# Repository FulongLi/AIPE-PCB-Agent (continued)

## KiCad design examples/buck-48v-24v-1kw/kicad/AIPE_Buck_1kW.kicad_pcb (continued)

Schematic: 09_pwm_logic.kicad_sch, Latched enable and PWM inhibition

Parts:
C69, C70, C71, C72: 100n/50V; C_0805_2012Metric
R51, R52: 33; R_0805_2012Metric
R53, R54, R55: 10k; R_0805_2012Metric
U12: SN74LVC1G74DCTR; SSOP-8_2.95x2.8mm_P0.65mm
U13: SN74LVC1G86DBVR; SOT-23-5
U14: SN74LVC1G08DBVR; SOT-23-5
U15: SN74LVC2G08DCTR; SSOP-8_2.95x2.8mm_P0.65mm

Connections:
3V3: C69.1, C70.1, C71.1, C72.1, U12.2 (D), U12.7 (PRE_N), U12.8 (VCC), U13.5 (VCC), U14.5 (VCC), U15.8 (VCC); also elsewhere on the board
ARM: R55.1, U12.1 (CLK); also elsewhere on the board
ARMED: U12.5 (Q), U14.1 (A); also elsewhere on the board
FAULT_N: U12.6 (CLR_N); also elsewhere on the board
GATE_OK: U14.4 (Y), U15.2 (1B), U15.6 (2B)
GND: C69.2, C70.2, C71.2, C72.2, R53.2, R54.2, R55.2, U12.4 (GND), U13.3 (GND), U14.3 (GND), U15.4 (GND); also elsewhere on the board
HI: R51.2; also elsewhere on the board
HI_LOGIC: R51.1, U15.7 (1Y)
LI: R52.2; also elsewhere on the board
LI_LOGIC: R52.1, U15.3 (2Y)
PWM_EXCLUSIVE: U13.4 (Y), U14.2 (B)
PWM_H: R53.1, U13.1 (A), U15.1 (1A); also elsewhere on the board
PWM_L: R54.1, U13.2 (B), U15.5 (2A); also elsewhere on the board

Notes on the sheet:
Latched enable and PWM inhibition

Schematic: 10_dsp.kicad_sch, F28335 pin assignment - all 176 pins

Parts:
U16: TMS320F28335PGFA; LQFP-176_24x24mm_P0.5mm

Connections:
1V9: U16.4 (VDD), U16.15 (VDD), U16.23 (VDD), U16.29 (VDD), U16.31 (VDD1A18), U16.59 (VDD2A18), U16.61 (VDD), U16.101 (VDD), U16.109 (VDD), U16.117 (VDD), U16.126 (VDD), U16.139 (VDD), U16.146 (VDD), U16.154 (VDD), U16.167 (VDD); also elsewhere on the board
3V3: U16.9 (VDDIO), U16.34 (VDDA2), U16.45 (VDDAIO), U16.71 (VDDIO), U16.84 (VDD3VFL), U16.93 (VDDIO), U16.107 (VDDIO), U16.121 (VDDIO), U16.143 (VDDIO), U16.159 (VDDIO), U16.170 (VDDIO); also elsewhere on the board
ADCBIAS: U16.57 (ADCRESEXT); also elsewhere on the board
ADCREFM: U16.55 (ADCREFM); also elsewhere on the board
ADCREFP: U16.56 (ADCREFP); also elsewhere on the board
ADC_CURRENT: U16.40 (ADCINA2); also elsewhere on the board
ADC_TEMP: U16.39 (ADCINA3); also elsewhere on the board
ADC_VIN: U16.42 (ADCINA0); also elsewhere on the board
ADC_VOUT: U16.41 (ADCINA1); also elsewhere on the board
ARM: U16.7 (GPIO2); also elsewhere on the board
BOOT84: U16.169 (GPIO84); also elsewhere on the board
BOOT85: U16.172 (GPIO85); also elsewhere on the board
BOOT86: U16.173 (GPIO86); also elsewhere on the board
BOOT87: U16.174 (GPIO87); also elsewhere on the board
CLK30: U16.105 (XCLKIN); also elsewhere on the board
EMU0: U16.85 (EMU0); also elsewhere on the board
EMU1: U16.86 (EMU1); also elsewhere on the board
FAULT_N: U16.21 (GPIO12); also elsewhere on the board
GND: U16.3 (VSS), U16.8 (VSS), U16.14 (VSS), U16.22 (VSS), U16.30 (VSS), U16.32 (VSS1AGND), U16.33 (VSSA2), U16.35 (ADCINA7), U16.36 (ADCINA6), U16.37 (ADCINA5), U16.38 (ADCINA4), U16.43 (ADCLO), U16.44 (VSSAIO), U16.46 (ADCINB0), U16.47 (ADCINB1), U16.48 (ADCINB2), U16.49 (ADCINB3), U16.50 (ADCINB4), U16.51 (ADCINB5), U16.52 (ADCINB6), U16.53 (ADCINB7), U16.54 (ADCREFIN), U16.58 (VSS2AGND), U16.60 (VSS), U16.70 (VSS), U16.83 (VSS), U16.92 (VSS), U16.103 (VSS), U16.104 (X1), U16.106 (VSS), U16.108 (VSS), U16.118 (VSS), U16.120 (VSS), U16.125 (VSS), U16.140 (VSS), U16.144 (VSS), U16.147 (VSS), U16.155 (VSS), U16.160 (VSS), U16.166 (VSS), U16.171 (VSS); also elsewhere on the board
PWM_H: U16.5 (GPIO0); also elsewhere on the board
PWM_L: U16.6 (GPIO1); also elsewhere on the board
TCK: U16.87 (TCK); also elsewhere on the board
TDI: U16.76 (TDI); also elsewhere on the board
TDO: U16.77 (TDO); also elsewhere on the board
TMS: U16.79 (TMS); also elsewhere on the board
TRST: U16.78 (TRST); also elsewhere on the board
UART_RX: U16.141 (GPIO28); also elsewhere on the board
UART_TX: U16.2 (GPIO29); also elsewhere on the board
XRS_N: U16.80 (XRS); also elsewhere on the board

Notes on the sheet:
F28335 pin assignment - all 176 pins
Units: supply pins / ADC / connected digital pins / intentionally unused digital pins. TEST1, TEST2 and X2 are NC.

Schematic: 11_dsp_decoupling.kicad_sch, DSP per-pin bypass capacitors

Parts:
C73, C74, C75, C76, C77, C78, C79, C80, C81, C82, C83, C84, C85, C86, C87, C88, C89, C90, C91, C92, C93, C94, C95, C96, C97, C98: 100n/50V; C_0805_2012Metric
C99, C100, C101, C102: 2.2u/25V; C_0805_2012Metric

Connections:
1V9: C73.1, C75.1, C76.1, C77.1, C78.1, C81.1, C82.1, C86.1, C88.1, C89.1, C91.1, C92.1, C94.1, C95.1, C97.1, C99.1, C100.1; also elsewhere on the board
3V3: C74.1, C79.1, C80.1, C83.1, C84.1, C85.1, C87.1, C90.1, C93.1, C96.1, C98.1, C101.1, C102.1; also elsewhere on the board
GND: C73.2, C74.2, C75.2, C76.2, C77.2, C78.2, C79.2, C80.2, C81.2, C82.2, C83.2, C84.2, C85.2, C86.2, C87.2, C88.2, C89.2, C90.2, C91.2, C92.2, C93.2, C94.2, C95.2, C96.2, C97.2, C98.2, C99.2, C100.2, C101.2, C102.2; also elsewhere on the board

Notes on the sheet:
DSP per-pin bypass capacitors

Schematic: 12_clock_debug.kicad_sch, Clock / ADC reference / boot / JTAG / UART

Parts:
C103, C104: 2.2u/25V; C_0805_2012Metric
C105: 100n/50V; C_0805_2012Metric
J7: TI 14-pin JTAG; key pin 6 absent; PinHeader_2x07_P2.54mm_Vertical
J8: BOOT: 1-2 SCI / 2-3 or open Flash; PinHeader_1x03_P2.54mm_Vertical
J9: UART 3.3 V only; PinHeader_1x03_P2.54mm_Vertical
R56: 22k; R_0805_2012Metric
R57: 33; R_0805_2012Metric
R58, R59, R60, R61, R62, R63, R64, R65: 4.7k; R_0805_2012Metric
R66: 2.2k; R_0805_2012Metric
R67, R68: 10k; R_0805_2012Metric
Y1: 30MHz/3V3; Oscillator_SMD_SeikoEpson_SG8002CA-4Pin_7.0x5.0mm

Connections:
3V3: C105.1, J7.5, J8.3, R58.1, R59.1, R60.1, R61.1, R62.1, R63.1, R64.1, R65.1, R68.1, Y1.1 (OE), Y1.4 (VDD); also elsewhere on the board
ADCBIAS: R56.1; also elsewhere on the board
ADCREFM: C103.1; also elsewhere on the board
ADCREFP: C104.1; also elsewhere on the board
BOOT84: J8.2, R58.2; also elsewhere on the board
BOOT85: R59.2; also elsewhere on the board
BOOT86: R60.2; also elsewhere on the board
BOOT87: R61.2; also elsewhere on the board
CLK30: R57.2; also elsewhere on the board
CLK30_SOURCE: R57.1, Y1.3 (OUT)
EMU0: J7.13, R62.2; also elsewhere on the board
EMU1: J7.14, R63.2; also elsewhere on the board
GND: C103.2, C104.2, C105.2, J7.4, J7.8, J7.10, J7.12, J8.1, J9.3, R56.2, R66.2, R67.2, Y1.2 (GND); also elsewhere on the board
TCK: J7.9, J7.11, R67.1; also elsewhere on the board
TDI: J7.3, R65.2; also elsewhere on the board
TDO: J7.7; also elsewhere on the board
TMS: J7.1, R64.2; also elsewhere on the board
TRST: J7.2, R66.1; also elsewhere on the board
UART_RX: J9.2, R68.2; also elsewhere on the board
UART_TX: J9.1; also elsewhere on the board

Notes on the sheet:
Clock / ADC reference / boot / JTAG / UART

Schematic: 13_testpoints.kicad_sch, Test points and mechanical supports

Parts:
H1, H2, H3, H4, H5, H6, H7, H8: M3 support; MountingHole_3.2mm_M3
TP1: VIN; TestPoint_Pad_D2.0mm
TP2: VOUT; TestPoint_Pad_D2.0mm
TP3: GND; TestPoint_Pad_D2.0mm
TP4: AUX12; TestPoint_Pad_D2.0mm
TP5: 5V; TestPoint_Pad_D2.0mm
TP6: 3V3; TestPoint_Pad_D2.0mm
TP7: 1V9; TestPoint_Pad_D2.0mm
TP8: FAULT_N; TestPoint_Pad_D2.0mm
TP9: ARMED; TestPoint_Pad_D2.0mm
TP10: ADC_CURRENT; TestPoint_Pad_D2.0mm
TP11: ADC_VOUT; TestPoint_Pad_D2.0mm
TP12: ADC_VIN; TestPoint_Pad_D2.0mm

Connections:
1V9: TP7.1; also elsewhere on the board
3V3: TP6.1; also elsewhere on the board
5V: TP5.1; also elsewhere on the board
ADC_CURRENT: TP10.1; also elsewhere on the board
ADC_VIN: TP12.1; also elsewhere on the board
ADC_VOUT: TP11.1; also elsewhere on the board
ARMED: TP9.1; also elsewhere on the board
AUX12: TP4.1; also elsewhere on the board
FAULT_N: TP8.1; also elsewhere on the board
GND: TP3.1; also elsewhere on the board
VIN: TP1.1; also elsewhere on the board
VOUT: TP2.1; also elsewhere on the board

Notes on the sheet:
Test points and mechanical supports
Flags: input source, fuse output, inductor output, auxiliary outputs through inductors, and bootstrap diode supply. They state supply provenance for ERC; they do not prove voltage, current capacity, or protection.

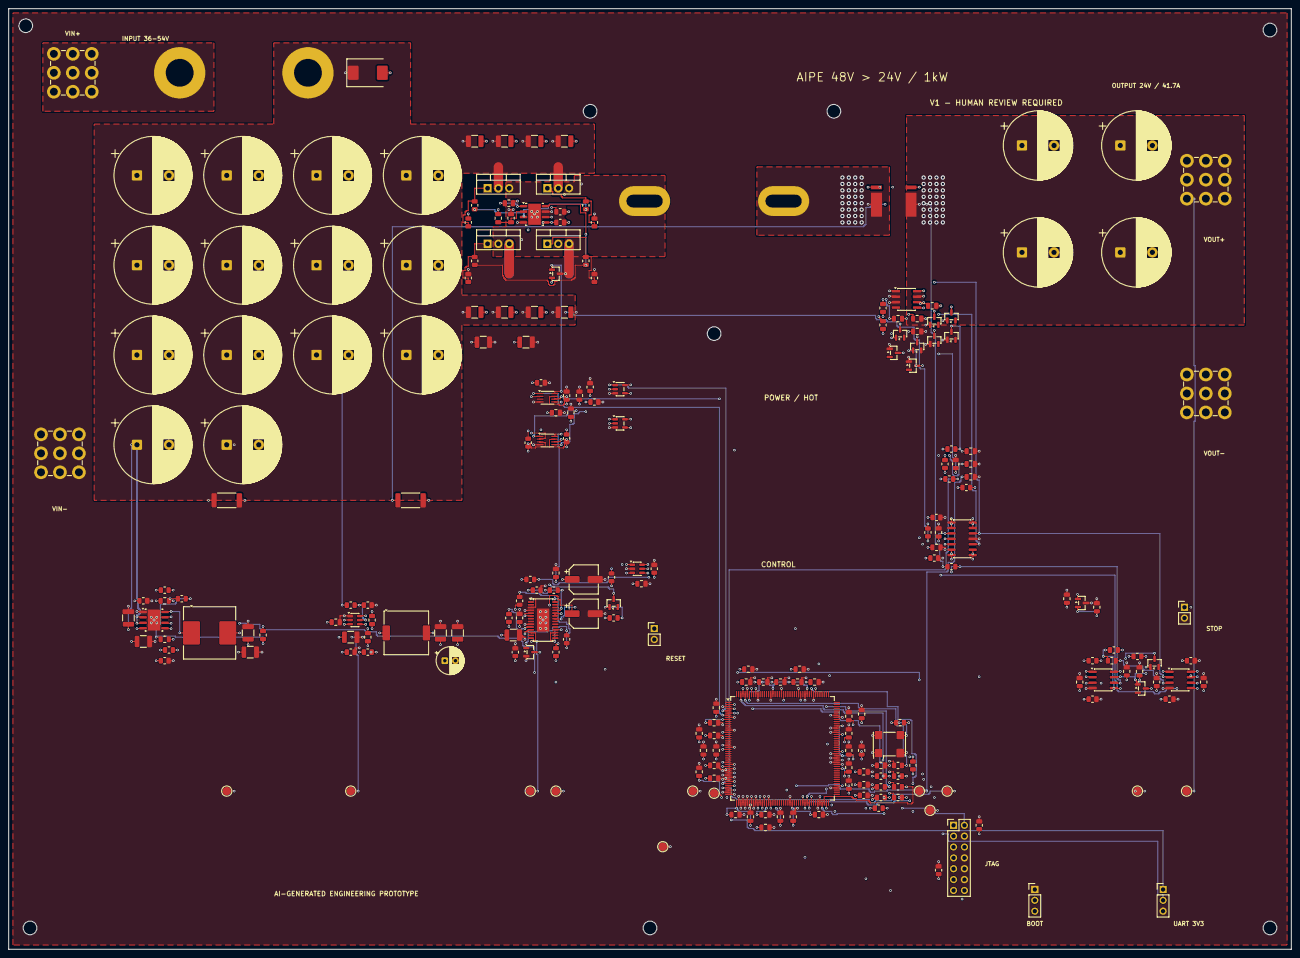
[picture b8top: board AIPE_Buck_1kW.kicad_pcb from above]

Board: 6 copper layers, 300.0 x 220.0 mm, 240 parts (0 on the bottom side), 85 nets.

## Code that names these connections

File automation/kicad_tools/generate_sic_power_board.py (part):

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output at the right.

Stage-3 corrections merged from verification/stage3_power_patch (zones-only DRC experiment at the structural floor):
chain parts on the pin-field pitch with courtyard-contained stubs, DAMP_MID bypass along the board edge, LED feeds,
terminals re-pitched for the REDCUBE pin-field gap, VIN In2 backbone clear of the VOUT In2 bar, HV ladders in one row
with via feeds, HV via rings and HV pads reserved for the auto-placer, VOUT_L without vias, PGND right strip stitched.

Only the kicad-cli DRC report counts as verification; the router report and the placement checks are geometric
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for _net in ('DESAT_H_A', 'DESAT_H_OC', 'DESAT_L_A', 'DESAT_L_OC', 'VIN_DIV', 'VOUT_DIV', 'ISO_RLIM', 'ISO_FB_VDD', 'ISO_FB_VEE',
             'HS_RLIM', 'HS_FB_VDD', 'HS_FB_VEE', 'LS_RLIM', 'LS_FB_VDD', 'LS_FB_VEE', 'HS_GK', 'LS_GK'):
    NET_RULES.setdefault(_net, dict(width=0.25, clearance=0.3))  # default width: these nets leave 0.65 mm pad rows through exact stubs
# VIN / VOUT potentials and their divider, bleeder and damping chains are never routed; every routed net (SW-, PGND-referenced
# or SELV) must keep the 3 mm outer-layer functional clearance from their pads, vias and chain tracks, so their router halo is 3 mm.
for _net in ('VIN', 'VIN_RAW', 'VOUT', 'VOUT_L', 'VIN_DIV_T1', 'VIN_DIV_T2', 'VIN_DIV_T3', 'VOUT_DIV_T1', 'BLD_IN_1', 'BLD_IN_2',
             'IND_IN_1', 'IND_IN_2', 'IND_IN_3', 'BLD_OUT_1', 'IND_OUT_1', 'IND_OUT_2', 'DAMP_MID', 'SNUB_MID'):
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                'VIN_OUT', 'VOUT_OUT', 'VIN_AMP', 'VOUT_AMP', 'VIN_SENSE', 'VOUT_SENSE', 'FAN_TACH', 'FAULT_N', 'SPARE_',
                'RELAY_ON', 'RLY_G', 'K1_LOW', '12V_PROT']
SIGNAL_ORDER_TRIALS = 4  # plan order, short nets first, long nets first, then a seeded perturbation of the best - the best is kept
SIGNAL_PINNED = ['KS_H', 'KS_L', 'G_H', 'G_L', 'VDD_H', 'VEE_H', 'VDD_L', 'VEE_L', 'ISO_15V', '5V_ISO']  # routed first in every order trial: the Kelvin and gate nets and the island rails (0.35 mm) - the nets whose pads the 0.25 mm feedback nets would otherwise seal inside the packed regions
RIPUP_ROUNDS = 30  # grid_router rip-up negotiation after the best order trial (stage 5: direct routing of connections that became free, lane release; 7 of 20 rounds kept in b5)
ROUTING_STYLE_V21 = dict(diagonal=True, bend_penalty_cells=[0.6, 2.0], simplify='octilinear', arcs=True, straight_nets=['PE'])  # V2.1 grid_router
# geometry (plan key 'style'): 8-direction A* with bend penalties, final octilinear simplification and tangent arcs on the signal nets (zone/power
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    # terminals (REDCUBE pin-field gap: 13.5 mm pitch between the two input rows), precharge PTC, MOV.
    # r20 (LR-23): the corner pocket (J1 above, barrier below, 3.9 mm In1 / In2 passage east of it) can only hold a terminal whose
    # current never has to leave it: the relay input terminal J5 (VIN_RAW) now sits under J1 (VIN_RAW) - same net, joined by the
    # VIN_RAW pours over the two pin fields. The input return J2 (PGND) takes the open east position of the UPPER row, where the In1
    # return plane and the B.Cu PGND column reach it over their full width; the relay output terminal J6 (VIN) keeps the east position
    # of the lower row inside the VIN+ F.Cu band. The precharge PTC RT1 stays; its VIN_RAW pad is fed by a 2 mm B.Cu track from the
    # J1 / J5 pour (rt1_vin_raw_feed) that passes north of J2's pin field.
    # r20 (LR-25): the MOV RV1 (23 mm tall) leaves the fan-intake corridor west of the sink for the exhaust side east of J4 (VIN pin
    # into the In2 backbone, PGND pin into In1 / the B.Cu output block); RT1 (22 mm, PTC) stays: its VIN_RAW / VIN pads bridge the two
    # pours and no corridor-free position reaches both.
    'J1': (7.5, 112.0, 0), 'J5': (7.5, 129.0, 0), 'J2': (23.0, 112.0, 0), 'J6': (23.0, 129.0, 0), 'RT1': (35.5, 120.5, 270), 'RV1': (165.0, 88.5, 90),
    'J3': (162.2, 50.0, 0), 'J4': (162.2, 65.5, 0),  # r20: 1.2 mm east with the sink (pads stay >= 5 mm from the sink courtyard)
    # top band, west -> east on the courtyard pitch (same-net pads of neighbouring parts ~0.6 mm apart joined by stubs inside the
    # two courtyards where the .kicad_dru pin-field exceptions apply): bleeder R1-R3 (2512) ending in PGND, the indicator chain
    # reversed so that the LED D1's PGND pad abuts R3's PGND pad (via in the 2512) and R4's VIN pad lies in the VIN+ pour, then
    # the damping legs C16/R12 | R13/C17 (DAMP_MID bypass along the board edge)
    'R1': (47.0, 6.5, 0), 'R2': (54.8, 6.5, 0), 'R3': (62.6, 6.5, 0), 'D1': (68.8, 6.5, 0), 'R6': (73.4, 6.5, 180), 'R5': (78.1, 6.5, 180), 'R4': (82.8, 6.5, 180),
    'C16': (88.9, 6.5, 0), 'R12': (96.6, 6.5, 0), 'R13': (104.4, 6.5, 180), 'C17': (112.1, 6.5, 180),
    # PE group west of the heatsink base: the M4 stud pad (r 4.3) between the two Y2 capacitors (pad 1 VIN / PGND at the footprint
    # origin, PE pad 10 mm east), whose PE pads reach the stud by short B.Cu stubs; the link resistors sit on B.Cu with their
    # PGND pads just inside the PGND B.Cu column (x <= 43.4) and the MID / PE pads east of it (R15 PGND|MID, R16 MID|PE standing
    # vertically, R14 PGND|PE); the PE spine (B.Cu, x 58) joins R14 / R16 to the stud 5 mm from every HV_PGND / VIN item
    'C18': (32.5, 19.0, 0), 'C19': (32.5, 36.0, 0), 'R15': (45.65, 45.0, 0, 'B'), 'R16': (48.9, 53.0, 270, 'B'), 'R14': (45.65, 64.0, 0, 'B'),
    # barrier line (HV pins up): UCC14141 at 90, UCC21710 / AMC1311 / TMCS1133 at 270
    'U2': (77.5, BARRIER_Y, 90), 'U1': (96.25, BARRIER_Y, 270), 'U3': (124.0, BARRIER_Y, 270), 'U4': (142.75, BARRIER_Y, 90),
    'U5': (163.0, BARRIER_Y, 90), 'U6': (181.0, BARRIER_Y, 270), 'U7': (195.0, BARRIER_Y, 270), 'U10': (212.0, BARRIER_Y, 270),
    # DESAT diodes beside the drains (D3 on F.Cu with its VIN pad in the VIN+ band and the DESAT pad away from the Q1 drain pin,
    # D5 on B.Cu - angle 0: the mirrored SW pad faces Q2 pin 1 and is fed by a B.Cu track from that pin); the DNP snubber on F.Cu
    # east of Q2's pins above the LS island (R11 SW pad -> In2 strip via, C15 PGND pad -> In1 via; 3 mm from every other group)
    'D3': (84.5, 133.5, 270), 'D5': (121.0, 132.5, 0, 'B'), 'R11': (146.5, 125.0, 0), 'C15': (154.0, 125.0, 0),
    # V_GS probe loops (through-hole) upright beside the TO-247 courtyards of Q1 / Q2 (CR-11), below the silkscreen band and clear of the SW via group
    'TP1': (102.0, 126.0, 90, 'B'), 'TP2': (130.0, 126.0, 90, 'B'),  # pin 1 at the origin: the loop spans y 122.2 - 127.3
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    # PGND pad downwards (angle None: resolved at placement time from the pad order) so its in-pad via keeps 3 mm from the ladder pads
    # (ring top 136.475 vs pad edge 132.8); the VIN_DIV group under U6, the VOUT_DIV group beside the VOUT tap (the taps end in vias,
    # so both nets stay on B.Cu); 2.5 mm pitch leaves 1 mm gaps for the B.Cu tracks between the parts
    # HS gate network on B.Cu: the three gate resistors stand upright directly above their driver pins' stub vias (U1.6 HS_OUTL (94.375, 138.75),
    # U1.4 HS_OUTH (96.875, 138.75), U1.7 HS_CLMP (93.125, 138.5)) with the pin-side pad down and the G_H pad up; the pull-down R22, the
    # Kelvin-gate RC R23 / C21 in the row above, 3 mm below Q1's pins; the G_H pour (B.Cu, post-route) covers the rows. The shelf-packed
    # layout boxed R20.1 / R23.1 behind G_H and KS_H tracks (b5: 808 / 255 cells)
    'R21': (92.0, BIAS_ROW_A_Y, 'pad1_down', 'B'), 'R20': (94.6, BIAS_ROW_A_Y, 'pad1_down', 'B'), 'R19': (97.2, BIAS_ROW_A_Y, 'pad1_down', 'B'),
    'R22': (99.8, BIAS_ROW_A_Y, None, 'B'),  # pull-down: G_H pad up with the other G_H pads, KS_H down
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    **{r: 'ls_desat' for r in ('R42', 'R43', 'R44', 'C49', 'D6', 'C56', 'C57', 'C58', 'C59', 'C44', 'C46')},
    # sensing island: the AMC1311 filters stand upright under the ladder row
    # SELV strip: driver input filters, pull-ups, bias chokes and input capacitors, sense amplifiers, test points
    # the RESET_N and BIAS_EN input filters (consumers U1 / U3 pin 14, U2 / U4 / U5 pin 4) sit in the roomy selv_hs region
    **{r: 'selv_hs' for r in ('R17', 'C20', 'R18', 'C27', 'C28', 'R27', 'R28', 'R34', 'L2', 'C30', 'C31', 'C32', 'C33', 'TP6',
                              'R67', 'C78', 'R68', 'R69', 'C79', 'R70')},
    **{r: 'selv_ls' for r in ('R35', 'C40', 'R36', 'C47', 'C48', 'R45', 'R46', 'R52', 'L3', 'C50', 'C51', 'C52', 'C53', 'L4', 'C60', 'C61', 'C62',
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    'and the SELV strip (F.Cu / B.Cu; GND_CTRL on In1.Cu and 3V3 on In2.Cu are pours reached by the escape vias); every routed net is '
    'confined to its own routing region, so no island net can approach another HV group; the HV nets are excluded from routing and '
    'connected by the pours and via groups only.',
    'Stage 3 corrections (zones-only DRC experiment): chain parts on the pin-field pitch with courtyard-contained stubs, DAMP_MID bypass, '
    'LED / 1206 feeds through F.Cu zone patches and 3 mm vias, terminals re-pitched for the REDCUBE pin-field gap, VIN In2 backbone clear '
    'of the VOUT In2 bar, HV ladders in one row with via feeds, HV via rings and HV pads reserved for the auto-placer, VOUT_L without vias, '
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
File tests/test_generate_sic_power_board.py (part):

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
    def test_vssop_columns_fan_out_along_the_pad_axis(self):
        boxes = {}
        for i, net in enumerate(['VIN_SENSE', 'VIN_AMP_N', 'VIN_AMP_P', 'GND_CTRL'], 1):  # U8's west column: pads along y, escaping west
            x, y = 163.387, 168.025 + (i - 1) * 0.65
            boxes[('U8', str(i))] = dict(ref_pad=f'U8.{i}', bbox=[x - 0.8125, y - 0.25, x + 0.8125, y + 0.25], net=net, smd=True, xy=(x, y), size=(1.625, 0.5),
                                         layer='F', centre=(165.5, 169.0))
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        self.assertEqual(len(keepouts), len(stubs))
        by_net = {k['net']: k for k in keepouts}
        half, depth = g.CONNECTOR_PORT_BOX
        south = by_net['RELAY_ON']  # outer-row pin going south
        self.assertAlmostEqual(south['rect'][1], g.CONNECTOR_STUB_END_Y['outer'] - 0.3, places=3)
        self.assertAlmostEqual(south['rect'][3], g.CONNECTOR_STUB_END_Y['outer'] + depth, places=3)
        flt = by_net['FLT_H_N']  # inner-row pin: jogs west, port half a pitch deeper
        self.assertAlmostEqual((flt['rect'][0] + flt['rect'][2]) / 2, 208.46 - g.CONNECTOR_JOG_MM, places=3)
        self.assertAlmostEqual(flt['rect'][1], g.CONNECTOR_STUB_END_Y['inner'] - 0.3, places=3)

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
    def test_plan_pins_the_kelvin_gate_and_rail_nets_first_in_every_trial(self):
        self.assertIn('signal_pinned', gr.PLAN_KEYS)
        self.assertEqual(g.SIGNAL_PINNED[:4], ['KS_H', 'KS_L', 'G_H', 'G_L'])
        self.assertNotIn('3V3', g.SIGNAL_PINNED)  # 3V3 first made the strip worse (r13): it keeps its early place in the plan order only
        self.assertLess(g.SIGNAL_ORDER.index('3V3'), g.SIGNAL_ORDER.index('PWM_'))
        self.assertAlmostEqual(gr.point_segment_distance(0.0, 1.0, -1.0, 0.0, 1.0, 0.0), 1.0)
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
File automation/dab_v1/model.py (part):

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        nets.update({3: 'PG_BIAS_N', 4: 'BIAS_ENF', 6: vin, 7: vin, 28: vdd, 29: vdd, 32: rlim, 33: fbvee, 34: fbvdd, 35: quiet})
        u = pp.bias_module(c, nets, page, vee_type='passive' if sense else 'power_out',
                           note=f'{bias["mpn"]}: VDD-VEE {"16 V, COM 5 V above VEE" if sense else "19 V, COM 4 V above VEE (+15 / -4 V gate rails)"}; '
                                'VEEA quiet star at pin 36 through the net tie; PG open-drain wired-AND on PG_BIAS_N')
        u['island'] = label
        tie = c.add('NT', 'VEEA STAR', 'NetTie:NetTie-2_SMD_Pad0.5mm', {1: quiet, 2: vee}, page=page, kind='passive',
                    note=f'Physical star point at {u["ref"]} pin 36; no load current through the quiet branch')
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        resistor(c, '4.7k', '3V3', 'NRST', p)
        cap(c, '10n/50V/0603', 'RESET_CT', GND, p)
        cap(c, '100n/50V/0603', '3V3', GND, p)
        c.add('J', 'MANUAL RESET', 'Connector_PinHeader_2.54mm:PinHeader_1x02_P2.54mm_Vertical', {1: 'MR_N', 2: GND}, page=p, kind='J', mpn='TSW-102-07-G-S',
              maker='Samtec', source='https://www.samtec.com/products/tsw', ref='J8')
    p = '02_card'
    card = iface['controlcard']
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            cap(c, '10u/25V/1210', '12V_E', GND, p)
        cap(c, '10u/25V/1210', '3V3', GND, p)
    with c.block('indicators', 'Status indicators'):
        for name, net, drive in (('PWR', 'LED_PWR_K', '3V3'), ('RUN', 'LED_RUN_K', 'GPIO_LED_RUN'), ('FAULT', 'LED_FAULT_K', 'TRIPPED')):
            c.add('D', f'LED {name}', 'LED_SMD:LED_0805_2012Metric', {1: net, 2: drive}, page=p, kind='D', mpn='LTST-C170KGKT' if name != 'FAULT' else 'LTST-C170KRKT',
                  maker='Lite-On', source='https://optoelectronics.liteon.com/en-global/led/LED-Component/Detail/926', definitions=pin_defs('1:K:passive 2:A:passive'))
            resistor(c, '1.5k', net, GND, p)
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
